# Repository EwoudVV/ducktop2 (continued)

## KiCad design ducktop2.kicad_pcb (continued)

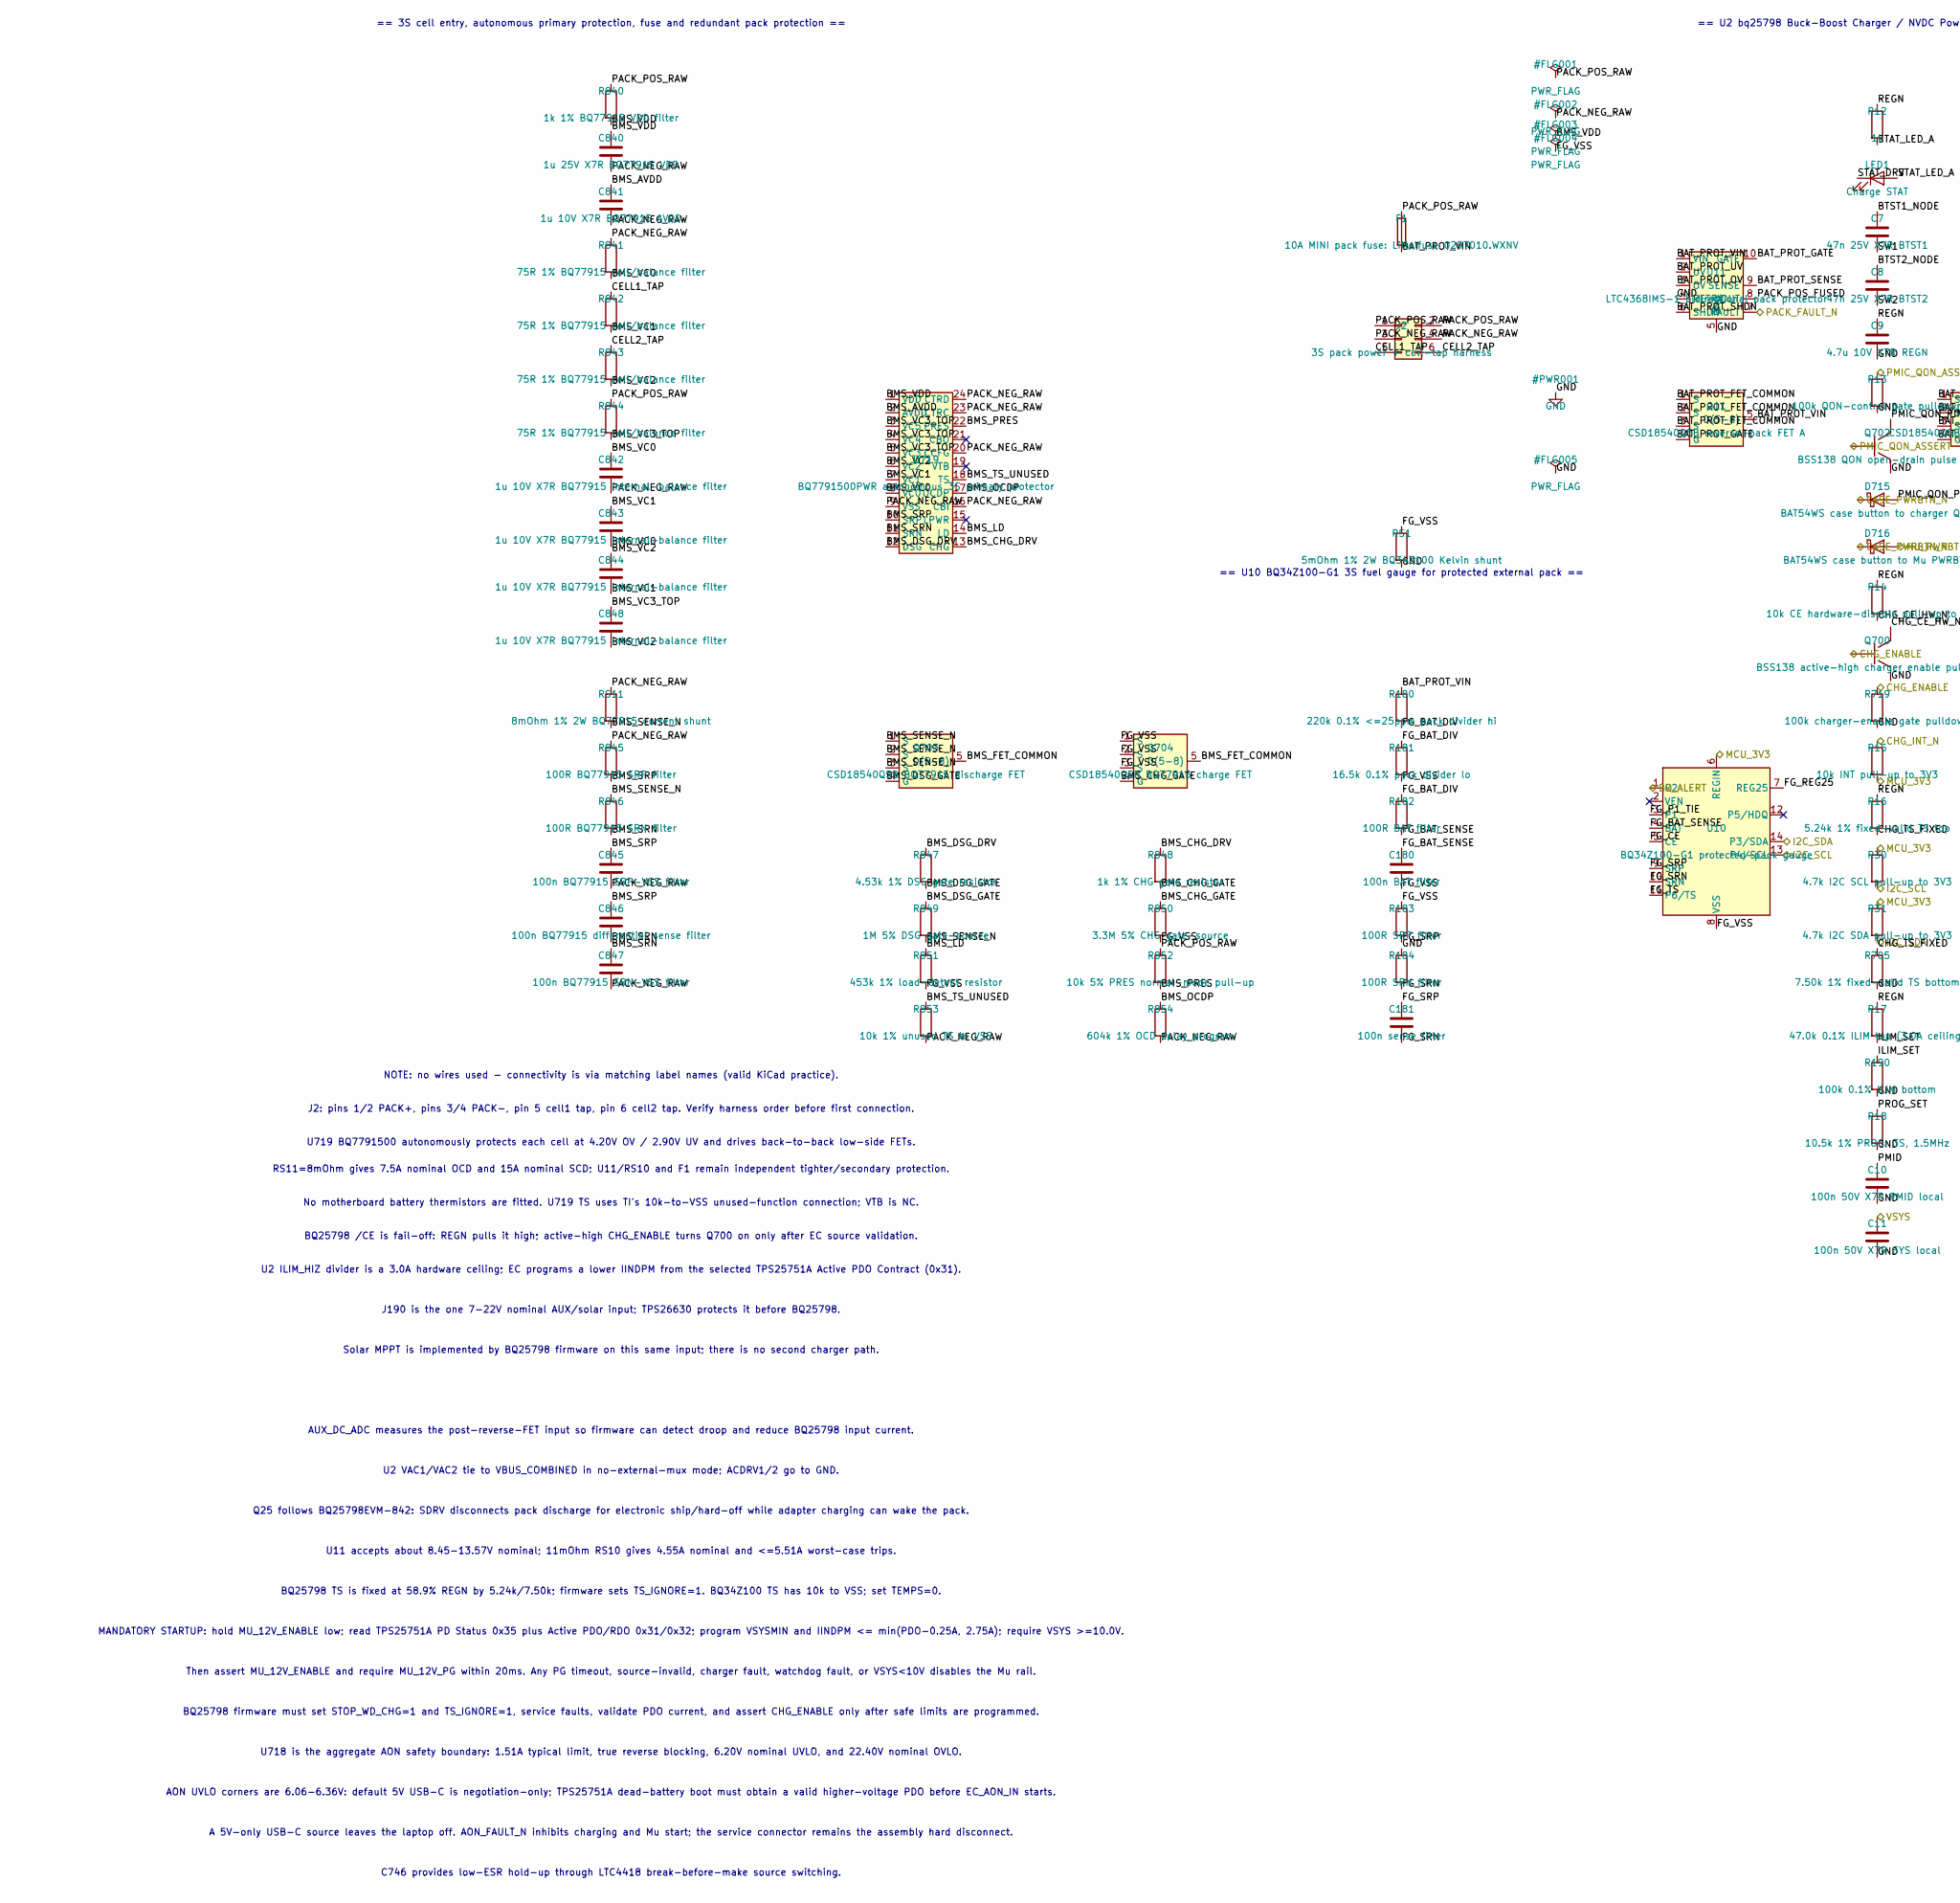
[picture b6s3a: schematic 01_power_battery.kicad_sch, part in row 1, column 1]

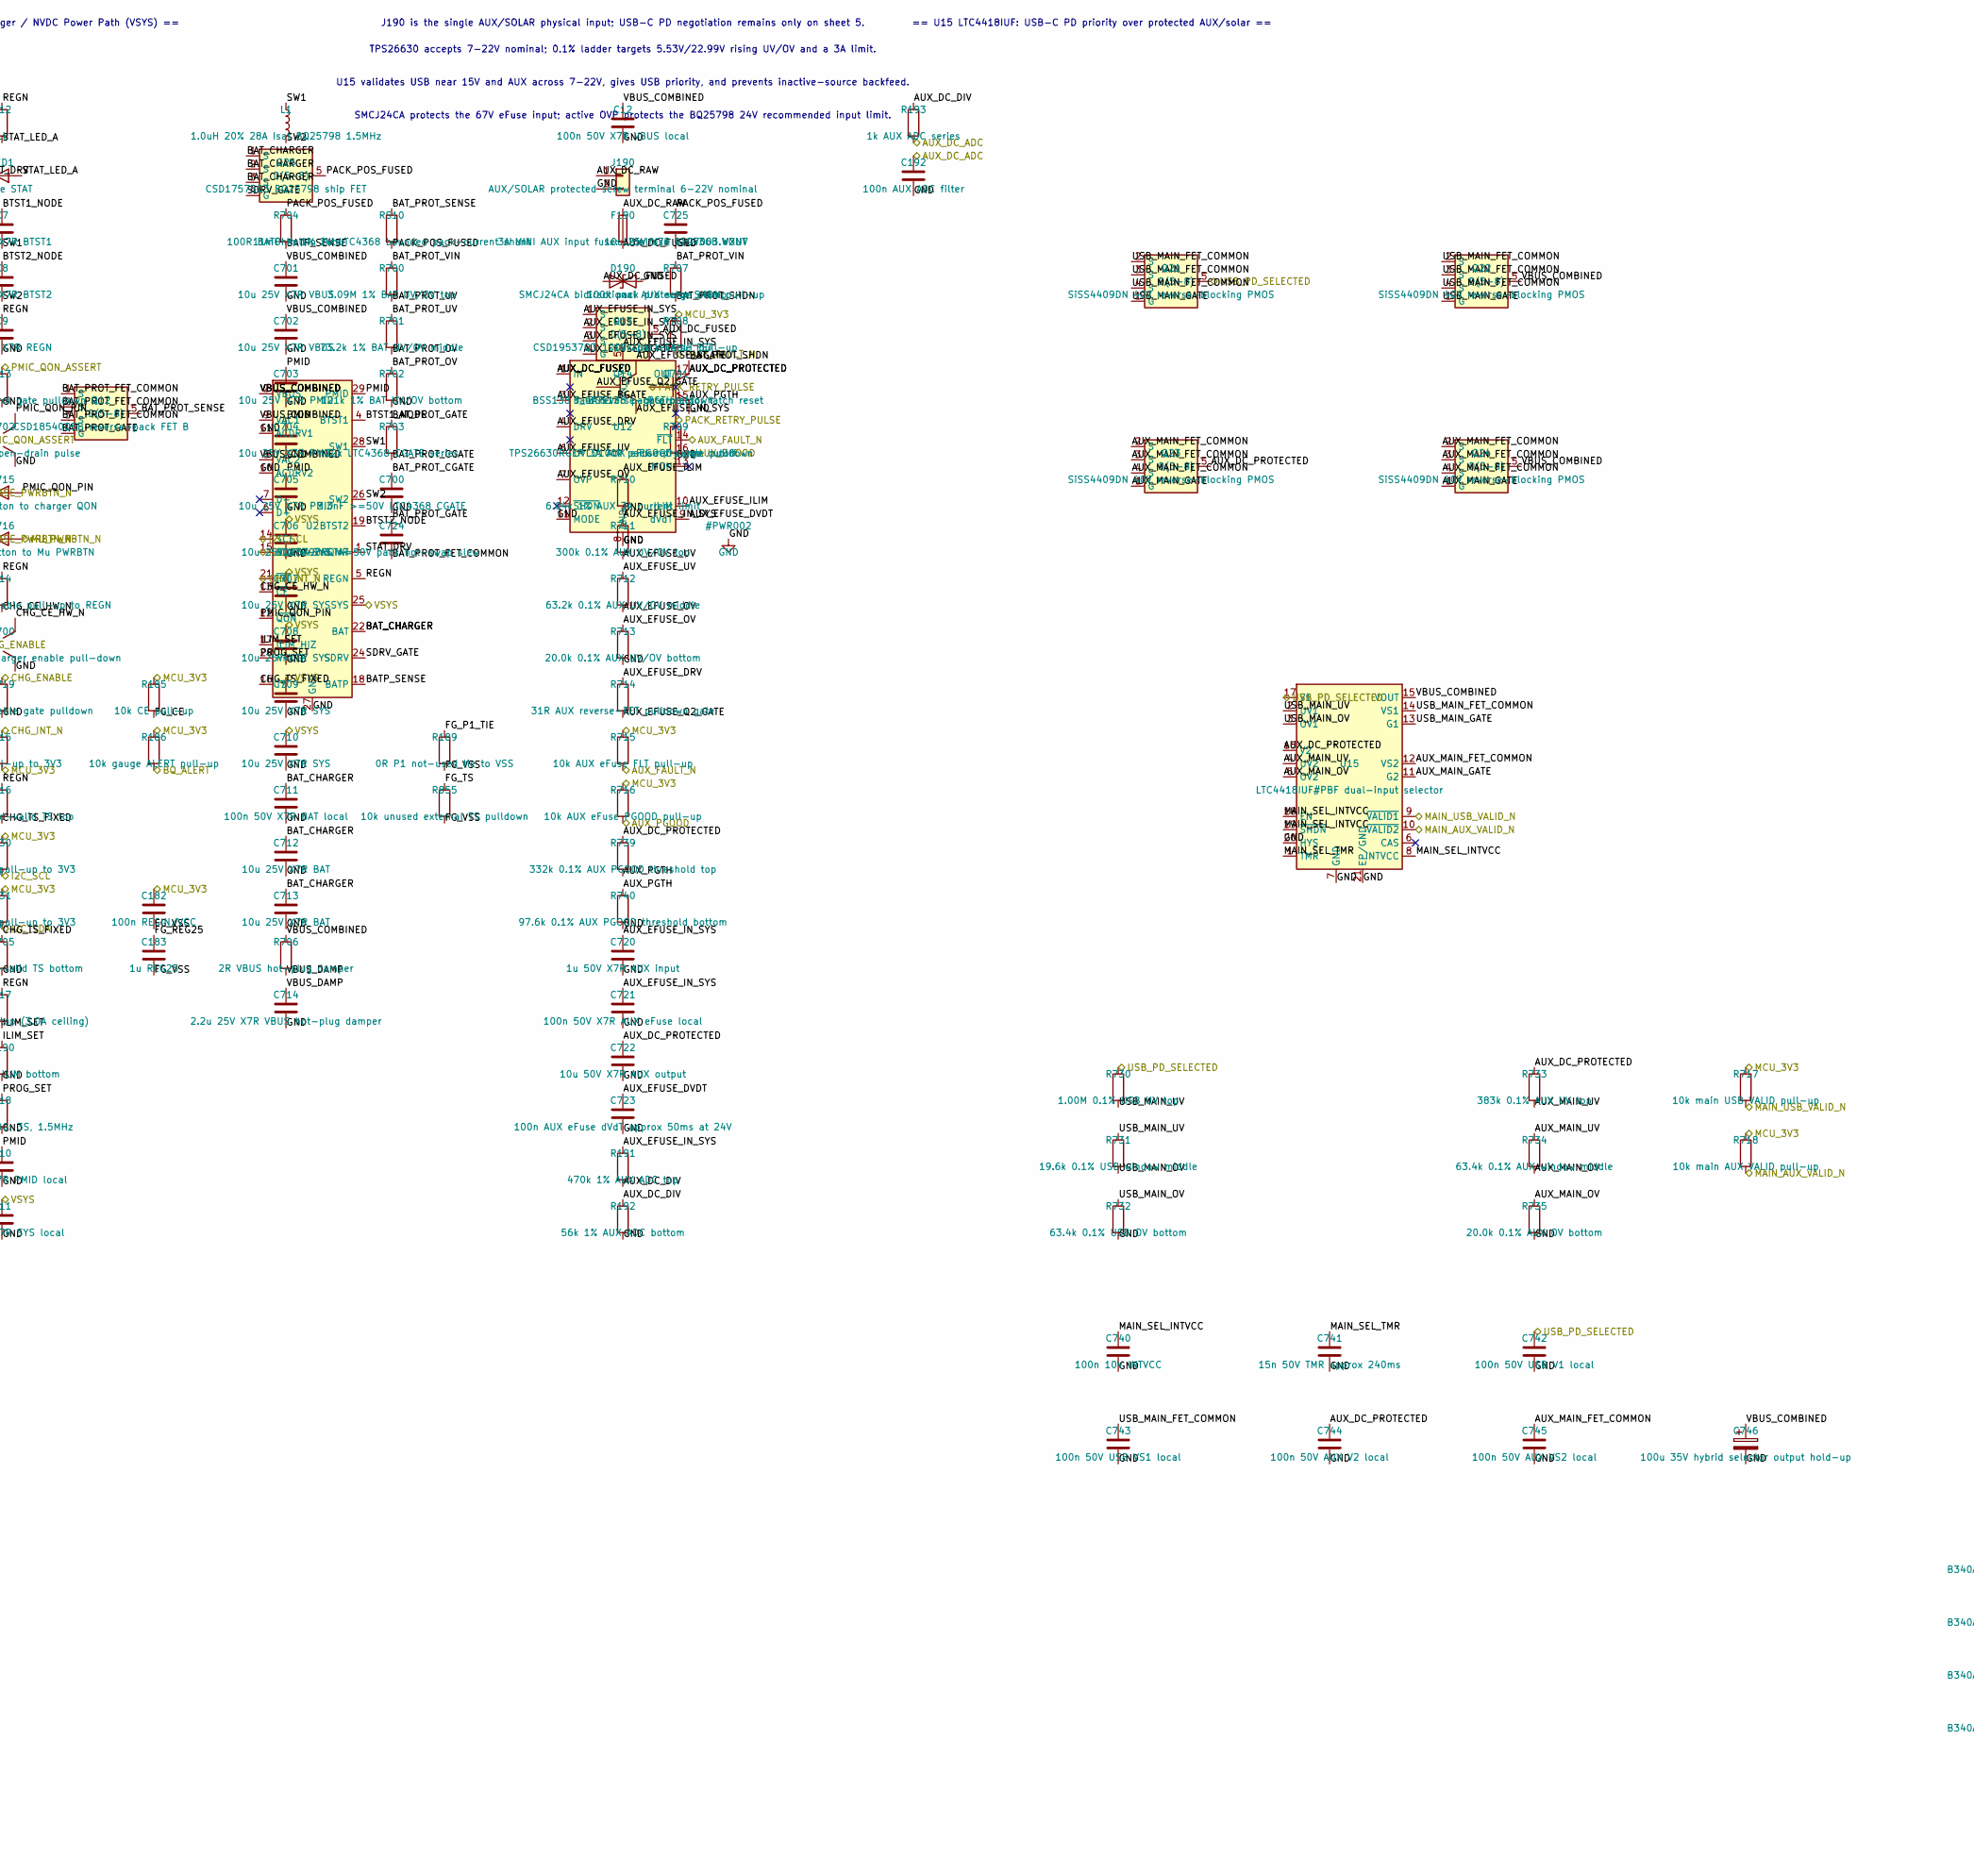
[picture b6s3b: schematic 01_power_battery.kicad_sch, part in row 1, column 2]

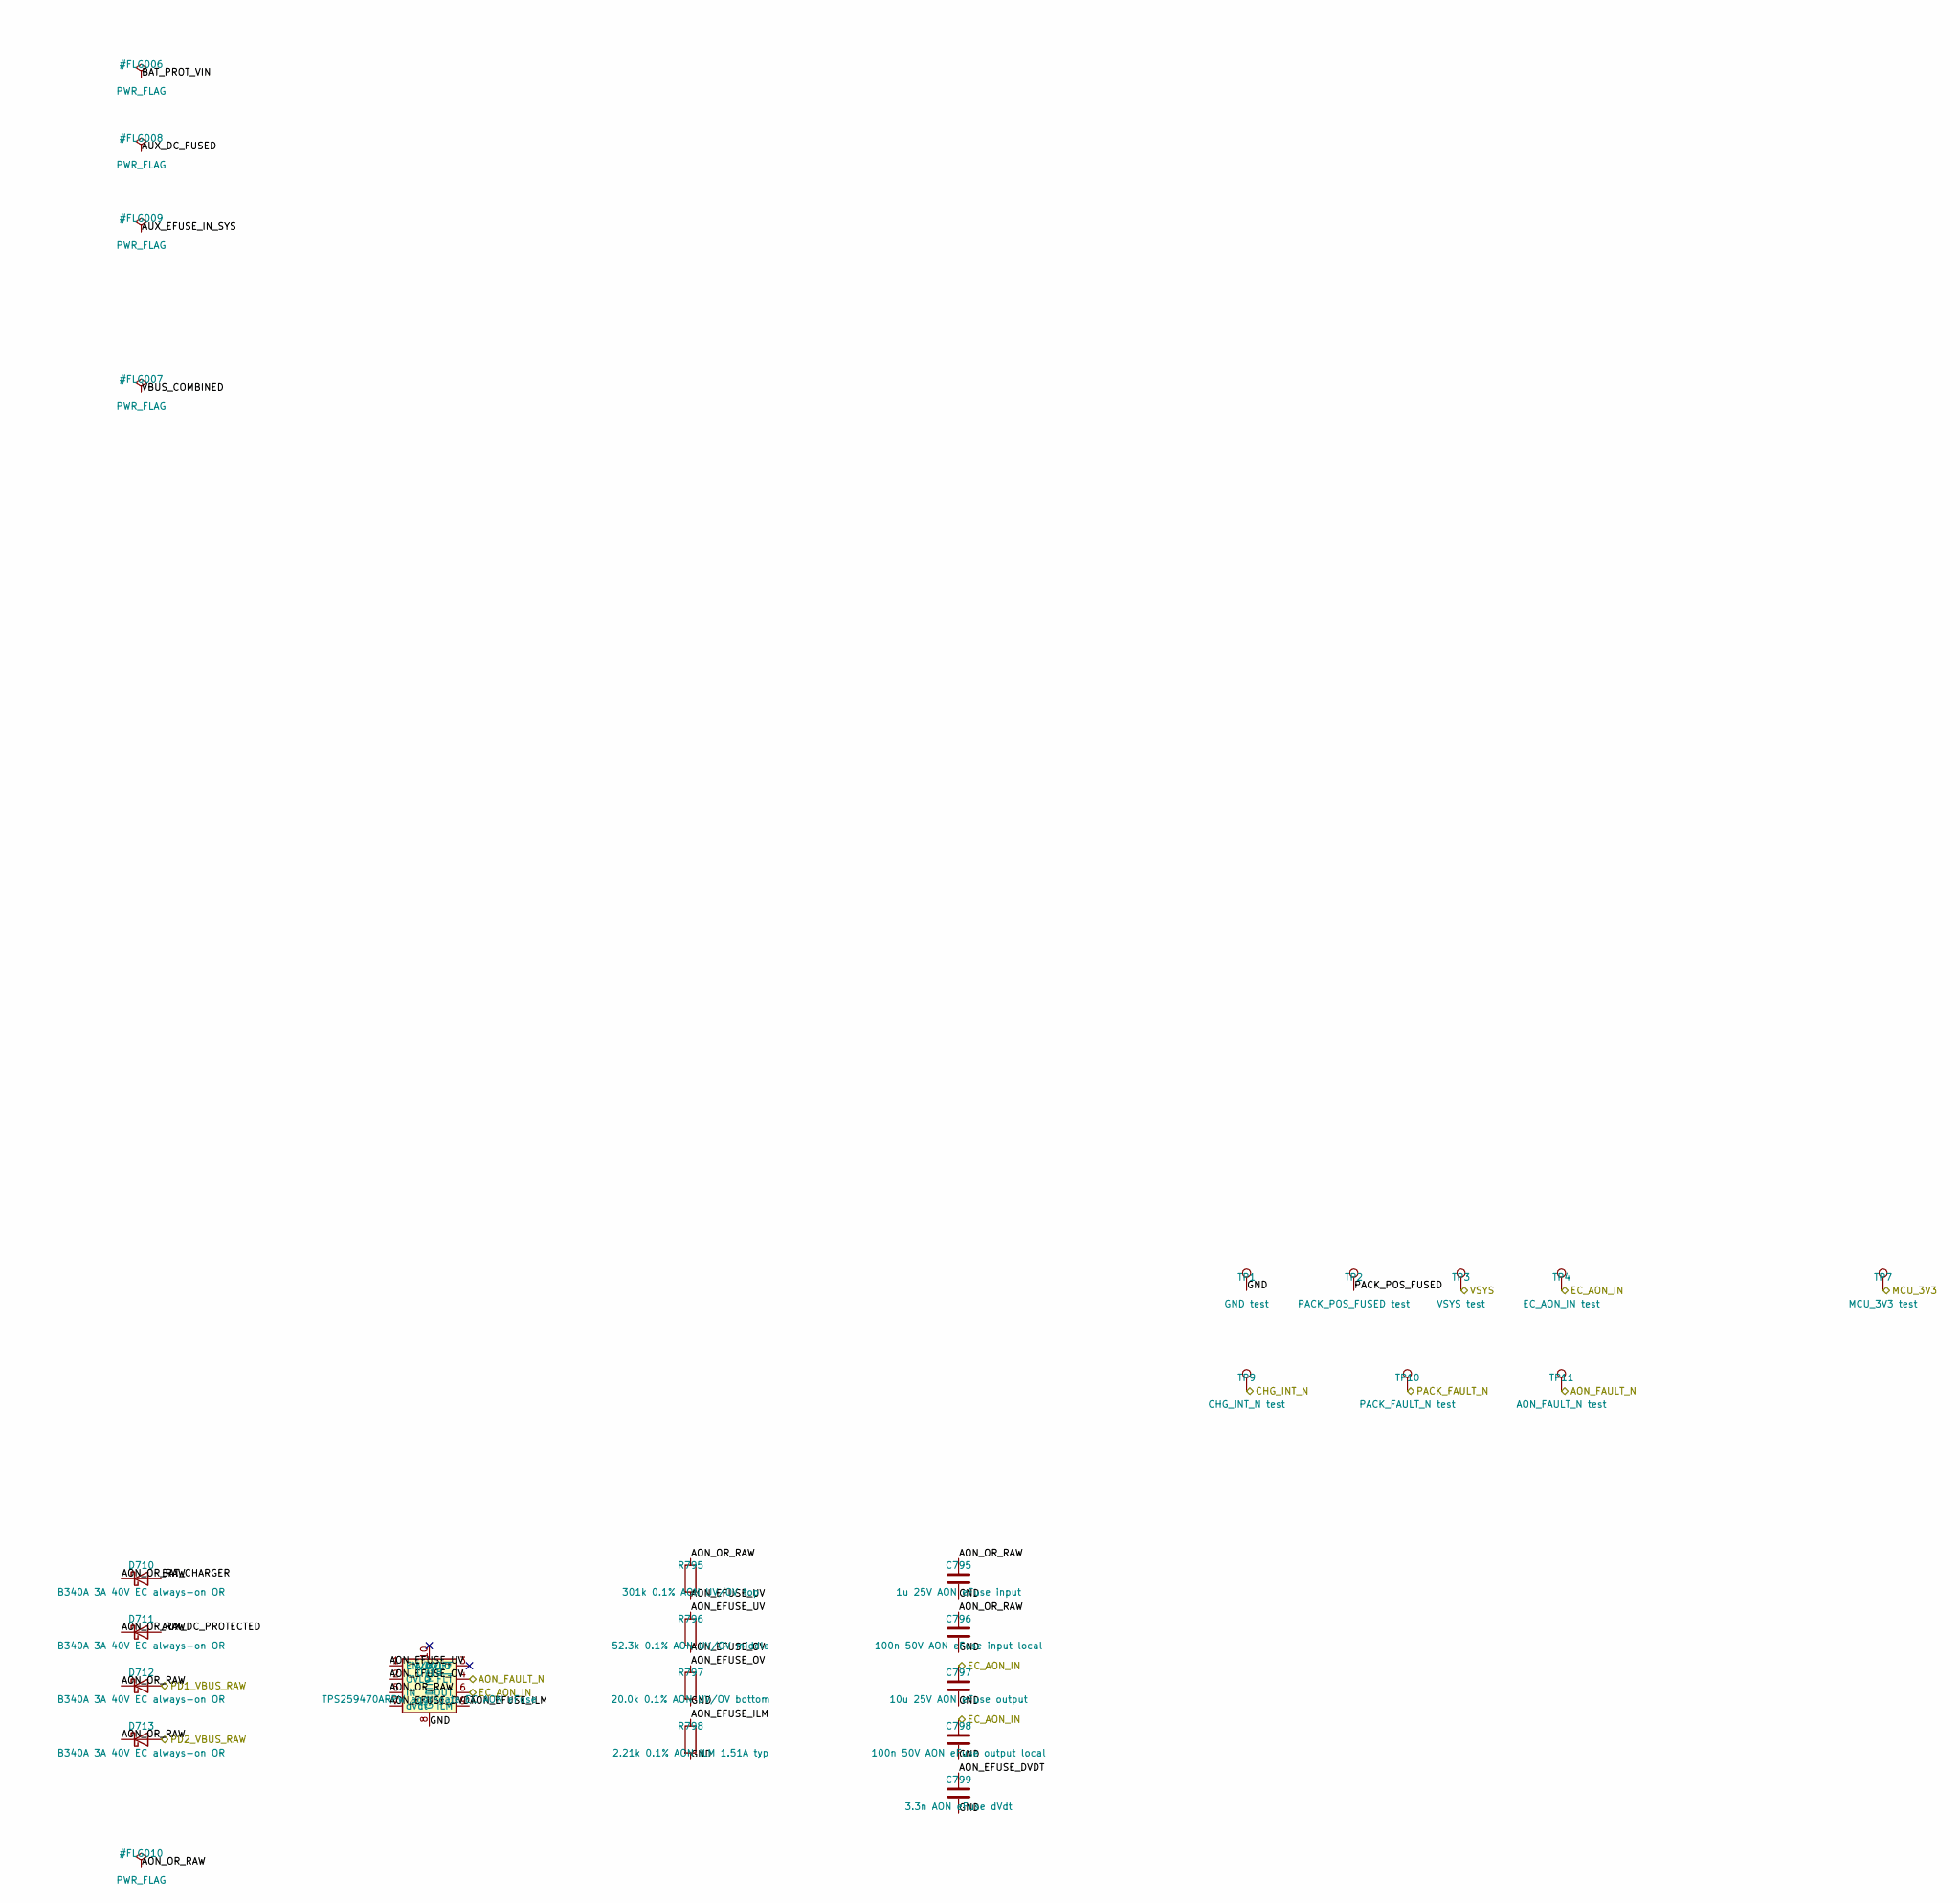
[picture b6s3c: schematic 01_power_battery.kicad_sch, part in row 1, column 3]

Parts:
C7: 47n 25V X7R BTST1; C_0402_1005Metric; MPN GRM155R71E473KA88D
C8: 47n 25V X7R BTST2; C_0402_1005Metric; MPN GRM155R71E473KA88D
C9: 4.7u 10V X7R REGN; C_0805_2012Metric; MPN GRM21BR71A475KA73L
C10: 100n 50V X7R PMID local; C_0603_1608Metric; MPN GRM188R71H104KA93D
C11: 100n 50V X7R SYS local; C_0603_1608Metric; MPN GRM188R71H104KA93D
C12: 100n 50V X7R VBUS local; C_0603_1608Metric; MPN GRM188R71H104KA93D
C180: 100n BAT filter; C_0603_1608Metric; MPN GRM188R71H104KA93D
C181: 100n sense filter; C_0603_1608Metric; MPN GRM188R71H104KA93D
C182: 100n REGIN/VCC; C_0603_1608Metric; MPN GRM188R71H104KA93D
C183: 1u REG25; C_0805_2012Metric; MPN GRM21BR71A105KA01L
C192: 100n AUX ADC filter; C_0603_1608Metric; MPN GRM188R71H104KA93D
C700: 3.3nF >=50V LTC4368 CGATE; C_0402_1005Metric; MPN GRM155R71H332KA01
C701, C702: 10u 25V X7R VBUS; C_1206_3216Metric; MPN GRM31CR71E106KA12L
C703, C704, C705: 10u 25V X7R PMID; C_1206_3216Metric; MPN GRM31CR71E106KA12L
C706, C707, C708, C709, C710: 10u 25V X7R SYS; C_1206_3216Metric; MPN GRM31CR71E106KA12L
C711: 100n 50V X7R BAT local; C_0603_1608Metric; MPN GRM188R71H104KA93D
C712, C713: 10u 25V X7R BAT; C_1206_3216Metric; MPN GRM31CR71E106KA12L
C714: 2.2u 25V X7R VBUS hot-plug damper; C_0805_2012Metric; MPN GRM21BR71E225KA73L
C720: 1u 50V X7R AUX input; C_0805_2012Metric; MPN GRM21BR71H105KA01
C721: 100n 50V X7R AUX eFuse local; C_0603_1608Metric; MPN GRM188R71H104KA93D
C722: 10u 50V X7R AUX output; C_1206_3216Metric; MPN CGA5L1X7R1H106K160AC
C723: 100n AUX eFuse dVdT approx 50ms at 24V; C_0603_1608Metric; MPN GRM188R71H104KA93D
C724: 4.7nF >=50V pack hot-swap slew; C_0402_1005Metric; MPN GRM155R71H472KA01
C725: 10u 25V X7R LTC4368 VOUT; C_0805_2012Metric; MPN GRM21BZ71E106KE15L
C740: 100n 10V INTVCC; C_0603_1608Metric; MPN GRM188R71A104KA61D
C741: 15n 50V TMR approx 240ms; C_0402_1005Metric; MPN GRM155R71H153KA12D
C742: 100n 50V USB V1 local; C_0603_1608Metric; MPN GRM188R71H104KA93D
C743: 100n 50V USB VS1 local; C_0603_1608Metric; MPN GRM188R71H104KA93D
C744: 100n 50V AUX V2 local; C_0603_1608Metric; MPN GRM188R71H104KA93D
C745: 100n 50V AUX VS2 local; C_0603_1608Metric; MPN GRM188R71H104KA93D
C746: 100u 35V hybrid selector output hold-up; CP_Elec_6.3x5.8; MPN EEHZK1V101XP
C795: 1u 25V AON eFuse input; C_0805_2012Metric; MPN GRM21BR71H105KA12L
C796: 100n 50V AON eFuse input local; C_0603_1608Metric; MPN GRM188R71H104KA93D
C797: 10u 25V AON eFuse output; C_1206_3216Metric; MPN GRM31CR71E106KA12L
C798: 100n 50V AON eFuse output local; C_0603_1608Metric; MPN GRM188R71H104KA93D
C799: 3.3n AON eFuse dVdt; C_0402_1005Metric; MPN GRM155R71H332KA01
C840: 1u 25V X7R BQ77915 VDD; C_0805_2012Metric; MPN GRM21BR71H105KA12L
C841: 1u 10V X7R BQ77915 AVDD; C_0805_2012Metric; MPN GRM21BR71A105KA01L
C842, C843, C844, C848: 1u 10V X7R BQ77915 internal-balance filter; C_0805_2012Metric; MPN GRM21BR71A105KA01L
C845: 100n BQ77915 SRP-VSS filter; C_0603_1608Metric; MPN GRM188R71H104KA93D
C846: 100n BQ77915 differential sense filter; C_0603_1608Metric; MPN GRM188R71H104KA93D
C847: 100n BQ77915 SRN-VSS filter; C_0603_1608Metric; MPN GRM188R71H104KA93D
D190: SMCJ24CA bidirectional AUX surge clamp; D_SMC; MPN SMCJ24CA-E3/57T
D710, D711, D712, D713: B340A 3A 40V EC always-on OR; D_SMA; MPN B340A-13-F
D715: BAT54WS case button to charger QON; D_SOD-323; MPN BAT54WS-7-F
D716: BAT54WS case button to Mu PWRBTN; D_SOD-323; MPN BAT54WS-7-F
F1: 10A MINI pack fuse: Littelfuse 0297010.WXNV; Fuseholder_Blade_Mini_Keystone_3568; MPN 0297010.WXNV + 3568
F190: 3A MINI AUX input fuse: Littelfuse 0297003.WXNV; Fuseholder_Blade_Mini_Keystone_3568; MPN 0297003.WXNV + 3568
J2: 3S pack power + cell-tap harness; Molex_Mega-Fit_76829-0006_2x03_P5.70mm_Vertical; MPN 76829-0006
J190: AUX/SOLAR protected screw terminal 6-22V nominal; TerminalBlock_Phoenix_MKDS-1,5-2-5.08_1x02_P5.08mm_Horizont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; MPN 1715022
L1: 1.0uH 20% 28A Isat BQ25798 1.5MHz; L_Coilcraft_XAL7030-102; MPN XAL7030-102MEC
LED1: Charge STAT; LED_0603_1608Metric; MPN APT1608SGC
Q11: CSD18540Q5B reverse-pack FET A; CSD18540Q5B_DNK; MPN CSD18540Q5B
Q12: CSD18540Q5B reverse-pack FET B; CSD18540Q5B_DNK; MPN CSD18540Q5B
Q13: CSD19537Q3 100V AUX reverse FET; CSD19537Q3_DQG; MPN CSD19537Q3
Q14: BSS138 fast reverse-gate pulldown; SOT-23; MPN BSS138LT1G
Q21, Q22, Q23, Q24: SiSS4409DN 40V reverse-blocking PMOS; Vishay_PowerPAK_1212-8_Single; MPN SiSS4409DN-T1-GE3
Q25: CSD17575Q3 BQ25798 ship FET; CSD19537Q3_DQG; MPN CSD17575Q3
Q700: BSS138 active-high charger enable pull-down; SOT-23; MPN BSS138LT1G
Q701: BSS138 pack protector latch reset; SOT-23; MPN BSS138LT1G
Q702: BSS138 QON open-drain pulse; SOT-23; MPN BSS138LT1G
Q703: CSD18540Q5B BQ77915 discharge FET; CSD18540Q5B_DNK; MPN CSD18540Q5B
Q704: CSD18540Q5B BQ77915 charge FET; CSD18540Q5B_DNK; MPN CSD18540Q5B
R12: 1k; R_0603_1608Metric; MPN RC0603FR-071KL
R13: 100k QON-control gate pulldown; R_0603_1608Metric; MPN RC0603FR-07100KL
R14: 10k CE hardware-disable pull-up to REGN; R_0603_1608Metric; MPN RC0603FR-0710KL
R15: 10k INT pull-up to 3V3; R_0603_1608Metric; MPN RC0603FR-0710KL
R16: 5.24k 1% fixed-valid TS top; R_0603_1608Metric; MPN RC0603FR-075K24L
R17: 47.0k 0.1% ILIM top (3.0A ceiling); R_0603_1608Metric; MPN RT0603BRD0747KL
R18: 10.5k 1% PROG: 3S, 1.5MHz; R_0603_1608Metric; MPN RC0603FR-0710K5L
R30: 4.7k I2C SCL pull-up to 3V3; R_0603_1608Metric; MPN RC0603FR-074K7L
R31: 4.7k I2C SDA pull-up to 3V3; R_0603_1608Metric; MPN RC0603FR-074K7L
R180: 220k 0.1% <=25ppm pack divider hi; R_0603_1608Metric; MPN RT0603BRD07220KL
R181: 16.5k 0.1% pack divider lo; R_0603_1608Metric; MPN RT0603BRD0716K5L
R182: 100R BAT filter; R_0603_1608Metric; MPN RC0603FR-07100RL
R183: 100R SRP filter; R_0603_1608Metric; MPN RC0603FR-07100RL
R184: 100R SRN filter; R_0603_1608Metric; MPN RC0603FR-07100RL
R185: 10k CE pull-up; R_0603_1608Metric; MPN RC0603FR-0710KL
R186: 10k gauge ALERT pull-up; R_0603_1608Metric; MPN RC0603FR-0710KL
R189: 0R P1 not-used tie to VSS; R_0603_1608Metric; MPN RC0603FR-070RL
R190: 100k 0.1% ILIM bottom; R_0603_1608Metric; MPN RT0603BRD07100KL
R191: 470k 1% AUX ADC top; R_0603_1608Metric; MPN RC0603FR-07470KL
R192: 56k 1% AUX ADC bottom; R_0603_1608Metric; MPN RC0603FR-0756KL
R193: 1k AUX ADC series; R_0603_1608Metric; MPN RC0603FR-071KL
R700: 3.09M 1% BAT UV/OV top; R_0603_1608Metric; MPN RC0603FR-073M09L
R701: 73.2k 1% BAT UV/OV middle; R_0603_1608Metric; MPN RC0603FR-0773K2L
R702: 121k 1% BAT UV/OV bottom; R_0603_1608Metric; MPN RC0603FR-07121KL
R703: 22k LTC4368 CGATE series; R_0603_1608Metric; MPN RC0603FR-0722KL
R704: 100R BATP Kelvin filter; R_0603_1608Metric; MPN RC0603FR-07100RL
R705: 7.50k 1% fixed-valid TS bottom; R_0603_1608Metric; MPN RC0603FR-077K50L
R706: 2R VBUS hot-plug damper; R_0603_1608Metric; MPN RC0603FR-072RL
R707: 100k pack protector SHDN pull-up; R_0603_1608Metric; MPN RC0603FR-07100KL
R708: 10k pack FAULT pull-up; R_0603_1608Metric; MPN RC0603FR-0710KL
R709: 100k pack retry gate pulldown; R_0603_1608Metric; MPN RC0603FR-07100KL
R710: 6.04k 1% AUX 3A current limit; R_0603_1608Metric; MPN RC0603FR-076K04L
R711: 300k 0.1% AUX UV/OV top; R_0603_1608Metric; MPN RT0603BRD07300KL
R712: 63.2k 0.1% AUX UV/OV middle; R_0603_1608Metric; MPN RT0603BRD0763K2L
R713: 20.0k 0.1% AUX UV/OV bottom; R_0603_1608Metric; MPN RT0603BRD0720K0L
R714: 31R AUX reverse-FET pulldown gate; R_0603_1608Metric; MPN RC0603FR-0731RL
R715: 10k AUX eFuse FLT pull-up; R_0603_1608Metric; MPN RC0603FR-0710KL
R716: 10k AUX eFuse PGOOD pull-up; R_0603_1608Metric; MPN RC0603FR-0710KL
R717: 10k main USB VALID pull-up; R_0603_1608Metric; MPN RC0603FR-0710KL
R718: 10k main AUX VALID pull-up; R_0603_1608Metric; MPN RC0603FR-0710KL
R719: 100k charger-enable gate pulldown; R_0603_1608Metric; MPN RC0603FR-07100KL
R730: 1.00M 0.1% USB UV top; R_0603_1608Metric; MPN RT0603BRD071ML
R731: 19.6k 0.1% USB window middle; R_0603_1608Metric; MPN RT0603BRD0719K6L
R732: 63.4k 0.1% USB OV bottom; R_0603_1608Metric; MPN RT0603BRD0763K4L
R733: 383k 0.1% AUX UV top; R_0603_1608Metric; MPN RT0603BRD07383KL
R734: 63.4k 0.1% AUX window middle; R_0603_1608Metric; MPN RT0603BRD0763K4L
R735: 20.0k 0.1% AUX OV bottom; R_0603_1608Metric; MPN RT0603BRD0720KL
R739: 332k 0.1% AUX PGOOD threshold top; R_0603_1608Metric; MPN RT0603BRD07332KL
R740: 97.6k 0.1% AUX PGOOD threshold bottom; R_0603_1608Metric; MPN RT0603BRD0797K6L
R795: 301k 0.1% AON UV/OV top; R_0603_1608Metric; MPN RT0603BRD07301KL
R796: 52.3k 0.1% AON UV/OV middle; R_0603_1608Metric; MPN RT0603BRD0752K3L
R797: 20.0k 0.1% AON UV/OV bottom; R_0603_1608Metric; MPN RT0603BRD0720KL
R798: 2.21k 0.1% AON ILM 1.51A typ; R_0603_1608Metric; MPN RT0603BRD072K21L
R840: 1k 1% BQ77915 VDD filter; R_0603_1608Metric; MPN RC0603FR-071KL
R841, R842, R843, R844: 75R 1% BQ77915 cell/balance filter; R_0603_1608Metric; MPN RC0603FR-0775RL
R845: 100R BQ77915 SRP filter; R_0603_1608Metric; MPN RC0603FR-07100RL
R846: 100R BQ77915 SRN filter; R_0603_1608Metric; MPN RC0603FR-07100RL
R847: 4.53k 1% DSG gate resistor; R_0603_1608Metric; MPN RC0603FR-074K53L
R848: 1k 1% CHG gate resistor; R_0603_1608Metric; MPN RC0603FR-071KL
R849: 1M 5% DSG gate-source; R_0603_1608Metric; MPN RC0603FR-071ML
R850: 3.3M 5% CHG gate-source; R_0603_1608Metric; MPN RC0603FR-073M3L
R851: 453k 1% load-detect resistor; R_0603_1608Metric; MPN RC0603FR-07453KL
R852: 10k 5% PRES normal-mode pull-up; R_0603_1608Metric; MPN RC0603FR-0710KL
R853: 10k 1% unused TS to VSS; R_0603_1608Metric; MPN RC0603FR-0710KL
R854: 604k 1% OCD delay program; R_0603_1608Metric; MPN RC0603FR-07604KL
R855: 10k unused external TS pulldown; R_0603_1608Metric; MPN RC0603FR-0710KL
RS1: 5mOhm 1% 2W BQ34Z100 Kelvin shunt; R_2512_6332Metric; MPN WSLP2512R0050FEA
RS10: 11mOhm 1% 2W LTC4368 bounded pack-current shunt; R_2512_6332Metric; MPN WSLP2512R0110FEA
RS11: 8mOhm 1% 2W BQ77915 current shunt; R_2512_6332Metric; MPN WSLP25128L000FEA
TP1: GND test; TestPoint_Pad_D1.0mm
TP2: PACK_POS_FUSED test; TestPoint_Pad_D1.0mm
TP3: VSYS test; TestPoint_Pad_D1.0mm
TP4: EC_AON_IN test; TestPoint_Pad_D1.0mm
TP7: MCU_3V3 test; TestPoint_Pad_D1.0mm
TP9: CHG_INT_N test; TestPoint_Pad_D1.0mm
TP10: PACK_FAULT_N test; TestPoint_Pad_D1.0mm
TP11: AON_FAULT_N test; TestPoint_Pad_D1.0mm
U2: BQ25798RQMR; Texas_RQM0029A_VQFN-29_4x4mm_P0.4mm; MPN BQ25798RQMR
U10: BQ34Z100-G1 protected-pack gauge; TSSOP-14_4.4x5mm_P0.65mm; MPN BQ34Z100PWR-G1
U11: LTC4368IMS-1 bidirectional pack protector; MSOP-10_3x3mm_P0.5mm; MPN LTC4368IMS-1#PBF
U12: TPS26630RGER 3A AUX eFuse / surge cutoff; Texas_RGE0024H_VQFN-24-1EP_4x4mm_P0.5mm_EP2.7x2.7mm_Thermal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; MPN TPS26630RGER
U15: LTC4418IUF#PBF dual-input selector; ADI_UF20_QFN20_4x4_P0.5_EP2.45; MPN LTC4418IUF#PBF
U718: TPS259470ARPW aggregate EC AON eFuse; Texas_RPW0010A_VQFN-HR-10_2x2mm; MPN TPS259470ARPW
U719: BQ7791500PWR autonomous 3S primary protector; TSSOP-24_4.4x7.8mm_P0.65mm; MPN BQ7791500PWR

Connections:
/AON_FAULT_N: TP11.1 (1_1), U718.4 (~FLT); also elsewhere on the board
/AUX_DC_ADC: C192.1, R193.2; also elsewhere on the board
/AUX_FAULT_N: R715.2, U12.14 (~FLT); also elsewhere on the board
/AUX_PGOOD: R716.2, U12.16 (PGOOD); also elsewhere on the board
/BQ_ALERT: R186.2, U10.1 (P2); also elsewhere on the board
/CASE_PWRBTN_N: D715.1 (K), D716.1 (K); also elsewhere on the board
/CHG_ENABLE: Q700.1 (G), R719.1; also elsewhere on the board
/CHG_INT_N: R15.1, TP9.1 (1_1), U2.21 (~INT); also elsewhere on the board
/EC_AON_IN: C797.1, C798.1, TP4.1 (1_1), U718.6 (OUT); also elsewhere on the board
/I2C_SCL: R30.2, U2.14 (SCL), U10.13 (P4/SCL); also elsewhere on the board
/I2C_SDA: R31.2, U2.15 (SDA), U10.14 (P3/SDA); also elsewhere on the board
/MAIN_AUX_VALID_N: R718.2, U15.10 (~VALID2); also elsewhere on the board
/MAIN_USB_VALID_N: R717.2, U15.9 (~VALID1); also elsewhere on the board
/MCU_3V3: C182.1, R15.2, R30.1, R31.1, R185.1, R186.1, R708.1, R715.1, R716.1, R717.1, R718.1, TP7.1 (1_1), U10.6 (REGIN); also elsewhere on the board
/MU_PWRBTN_N: D716.2 (A); also elsewhere on the board
/PACK_FAULT_N: R708.2, TP10.1 (1_1), U11.7 (FAULT); also elsewhere on the board
/PACK_RETRY_PULSE: Q701.1 (G), R709.1; also elsewhere on the board
/PD1_VBUS_RAW: D712.2 (A); also elsewhere on the board
/PD2_VBUS_RAW: D713.2 (A); also elsewhere on the board
/PMIC_QON_ASSERT: Q702.1 (G), R13.1; also elsewhere on the board
/Power & Battery/AON_EFUSE_DVDT: C799.1, U718.7 (dVdt)
/Power & Battery/AON_EFUSE_ILM: R798.1, U718.9 (ILM)
/Power & Battery/AON_EFUSE_OV: R796.2, R797.1, U718.2 (OVLO)
/Power & Battery/AON_EFUSE_UV: R795.2, R796.1, U718.1 (EN/UVLO)
/Power & Battery/AON_OR_RAW: C795.1, C796.1, D710.1 (K), D711.1 (K), D712.1 (K), D713.1 (K), R795.1, U718.5 (IN)
/Power & Battery/AUX_DC_DIV: R191.2, R192.1, R193.1
/Power & Battery/AUX_DC_FUSED: D190.1 (A1), F190.2, Q13.5 (D(5-8)), U12.1 (IN), U12.2 (IN)
/Power & Battery/AUX_DC_PROTECTED: C722.1, C744.1, D711.2 (A), Q23.5 (D(5-8)), R733.1, R739.1, U12.17 (OUT), U12.18 (OUT), U15.16 (V2)
/Power & Battery/AUX_DC_RAW: F190.1, J190.1
/Power & Battery/AUX_EFUSE_BGATE: Q13.4 (G), Q14.3 (D), U12.3 (B_GATE)
/Power & Battery/AUX_EFUSE_DRV: R714.1, U12.4 (DRV)
/Power & Battery/AUX_EFUSE_DVDT: C723.1, U12.9 (dVdT)
/Power & Battery/AUX_EFUSE_ILIM: R710.1, U12.10 (ILIM)
/Power & Battery/AUX_EFUSE_IN_SYS: C720.1, C721.1, Q13.1 (S), Q13.2 (S), Q13.3 (S), Q14.2 (S), R191.1, R711.1, U12.5 (IN_SYS)
/Power & Battery/AUX_EFUSE_OV: R712.2, R713.1, U12.7 (OVP)
/Power & Battery/AUX_EFUSE_Q2_GATE: Q14.1 (G), R714.2
/Power & Battery/AUX_EFUSE_UV: R711.2, R712.1, U12.6 (UVLO)
/Power & Battery/AUX_MAIN_FET_COMMON: C745.1, Q23.2 (S), Q23.3 (S), Q23.4 (S), Q24.2 (S), Q24.3 (S), Q24.4 (S), U15.12 (VS2)
/Power & Battery/AUX_MAIN_GATE: Q23.1 (G), Q24.1 (G), U15.11 (G2)
/Power & Battery/AUX_MAIN_OV: R734.2, R735.1, U15.5 (OV2)
/Power & Battery/AUX_MAIN_UV: R733.2, R734.1, U15.4 (UV2)
/Power & Battery/AUX_PGTH: R739.2, R740.1, U12.15 (PGTH)
/Power & Battery/BATP_SENSE: R704.2, U2.18 (BATP)
/Power & Battery/BAT_CHARGER: C711.1, C712.1, C713.1, D710.2 (A), Q25.1 (S), Q25.2 (S), Q25.3 (S), U2.22 (BAT), U2.23 (BAT)
/Power & Battery/BAT_PROT_CGATE: C700.1, R703.2
/Power & Battery/BAT_PROT_FET_COMMON: C724.2, Q11.1 (S), Q11.2 (S), Q11.3 (S), Q12.1 (S), Q12.2 (S), Q12.3 (S)
/Power & Battery/BAT_PROT_GATE: C724.1, Q11.4 (G), Q12.4 (G), R703.1, U11.10 (GATE)
/Power & Battery/BAT_PROT_OV: R701.2, R702.1, U11.3 (OV)
/Power & Battery/BAT_PROT_SENSE: Q12.5 (D(5-8)), RS10.1, U11.9 (SENSE)
/Power & Battery/BAT_PROT_SHDN: Q701.3 (D), R707.2, U11.6 (SHDN)
/Power & Battery/BAT_PROT_UV: R700.2, R701.1, U11.2 (UV)
/Power & Battery/BAT_PROT_VIN: F1.2, Q11.5 (D(5-8)), R180.1, R700.1, R707.1, U11.1 (VIN)
/Power & Battery/BMS_AVDD: C841.1, U719.2 (AVDD)
/Power & Battery/BMS_CHG_DRV: R848.1, U719.13 (CHG)
/Power & Battery/BMS_CHG_GATE: Q704.4 (G), R848.2, R850.1
/Power & Battery/BMS_DSG_DRV: R847.1, U719.12 (DSG)
/Power & Battery/BMS_DSG_GATE: Q703.4 (G), R847.2, R849.1
/Power & Battery/BMS_FET_COMMON: Q703.5 (D(5-8)), Q704.5 (D(5-8))
/Power & Battery/BMS_LD: R851.1, U719.14 (LD)
/Power & Battery/BMS_OCDP: R854.1, U719.17 (OCDP)
/Power & Battery/BMS_PRES: R852.2, U719.22 (PRES)
/Power & Battery/BMS_SENSE_N: Q703.1 (S), Q703.2 (S), Q703.3 (S), R846.1, R849.2, RS11.2
/Power & Battery/BMS_SRN: C846.2, C847.1, R846.2, U719.11 (SRN)
/Power & Battery/BMS_SRP: C845.1, C846.1, R845.2, U719.10 (SRP)
/Power & Battery/BMS_TS_UNUSED: R853.1, U719.18 (TS)
/Power & Battery/BMS_VC0: C842.1, C843.2, R841.2, U719.8 (VC0)
/Power & Battery/BMS_VC1: C843.1, C844.2, R842.2, U719.7 (VC1)
/Power & Battery/BMS_VC2: C844.1, C848.2, R843.2, U719.6 (VC2)
/Power & Battery/BMS_VC3_TOP: C848.1, R844.2, U719.3 (VC5), U719.4 (VC4), U719.5 (VC3)
/Power & Battery/BMS_VDD: C840.1, R840.2, U719.1 (VDD)
/Power & Battery/BTST1_NODE: C7.1, U2.4 (BTST1)
/Power & Battery/BTST2_NODE: C8.1, U2.19 (BTST2)
/Power & Battery/CELL1_TAP: J2.5, R842.1
/Power & Battery/CELL2_TAP: J2.6, R843.1
/Power & Battery/CHG_CE_HW_N: Q700.3 (D), R14.2, U2.13 (~CE)
/Power & Battery/CHG_TS_FIXED: R16.2, R705.1, U2.16 (TS)
/Power & Battery/FG_BAT_DIV: R180.2, R181.1, R182.1
/Power & Battery/FG_BAT_SENSE: C180.1, R182.2, U10.4 (BAT)
/Power & Battery/FG_CE: R185.2, U10.5 (CE)
/Power & Battery/FG_P1_TIE: R189.1, U10.3 (P1)
/Power & Battery/FG_REG25: C183.1, U10.7 (REG25)
/Power & Battery/FG_SRN: C181.2, R184.2, U10.10 (SRN)
/Power & Battery/FG_SRP: C181.1, R183.2, U10.9 (SRP)
/Power & Battery/FG_TS: R855.1, U10.11 (P6/TS)
/Power & Battery/FG_VSS: C180.2, C182.2, C183.2, Q704.1 (S), Q704.2 (S), Q704.3 (S), R181.2, R183.1, R189.2, R850.2, R851.2, R855.2, RS1.1, U10.8 (VSS)
/Power & Battery/ILIM_SET: R17.2, R190.1, U2.17 (ILIM_HIZ)
/Power & Battery/MAIN_SEL_INTVCC: C740.1, U15.8 (INTVCC), U15.18 (EN), U15.19 (~SHDN)
/Power & Battery/MAIN_SEL_TMR: C741.1, U15.1 (TMR)
/Power & Battery/PACK_NEG_RAW: C840.2, C841.2, C842.2, C845.2, C847.2, J2.3, J2.4, R841.1, R845.1, R853.2, R854.2, RS11.1, U719.9 (VSS), U719.16 (CBI), U719.20 (CCFG), U719.23 (CTRC), U719.24 (CTRD)
/Power & Battery/PACK_POS_FUSED: C725.1, Q25.5 (D(5-8)), R704.1, RS10.2, TP2.1 (1_1), U11.8 (VOUT)
/Power & Battery/PACK_POS_RAW: F1.1, J2.1, J2.2, R840.1, R844.1, R852.1
/Power & Battery/PMIC_QON_PIN: D715.2 (A), Q702.3 (D), U2.12 (~QON)
/Power & Battery/PMID: C10.1, C703.1, C704.1, C705.1, U2.29 (PMID)
/Power & Battery/PROG_SET: R18.1, U2.20 (PROG)
/Power & Battery/REGN: C9.1, R12.1, R14.1, R16.1, R17.1, U2.5 (REGN)
/Power & Battery/SDRV_GATE: Q25.4 (G), U2.24 (SDRV)
/Power & Battery/STAT_DRV: LED1.1 (K), U2.1 (STAT)
/Power & Battery/STAT_LED_A: LED1.2 (A), R12.2
/Power & Battery/SW1: C7.2, L1.1, U2.28 (SW1)
/Power & Battery/SW2: C8.2, L1.2, U2.26 (SW2)
/Power & Battery/USB_MAIN_FET_COMMON: C743.1, Q21.2 (S), Q21.3 (S), Q21.4 (S), Q22.2 (S), Q22.3 (S), Q22.4 (S), U15.14 (VS1)
/Power & Battery/USB_MAIN_GATE: Q21.1 (G), Q22.1 (G), U15.13 (G1)
/Power & Battery/USB_MAIN_OV: R731.2, R732.1, U15.3 (OV1)
/Power & Battery/USB_MAIN_UV: R730.2, R731.1, U15.2 (UV1)
/Power & Battery/VBUS_COMBINED: C12.1, C701.1, C702.1, C746.1, Q22.5 (D(5-8)), Q24.5 (D(5-8)), R706.1, U2.2 (VBUS), U2.3 (VBUS), U2.8 (VAC2), U2.9 (VAC1), U15.15 (VOUT)
/Power & Battery/VBUS_DAMP: C714.1, R706.2
/USB_PD_SELECTED: C742.1, Q21.5 (D(5-8)), R730.1, U15.17 (V1); also elsewhere on the board
/VSYS: C11.1, C706.1, C707.1, C708.1, C709.1, C710.1, TP3.1 (1_1), U2.25 (SYS); also elsewhere on the board
GND: C9.2, C10.2, C11.2, C12.2, C192.2, C700.2, C701.2, C702.2, C703.2, C704.2, C705.2, C706.2, C707.2, C708.2, C709.2, C710.2, C711.2, C712.2, C713.2, C714.2, C720.2, C721.2, C722.2, C723.2, C725.2, C740.2, C741.2, C742.2, C743.2, C744.2, C745.2, C746.2, C795.2, C796.2, C797.2, C798.2, C799.2, D190.2 (A2), J190.2, Q700.2 (S), Q701.2 (S), Q702.2 (S), R13.2, R18.2, R184.1, R190.2, R192.2, R702.2, R705.2, R709.2, R710.2, R713.2, R719.2, R732.2, R735.2, R740.2, R797.2, R798.2, RS1.2, TP1.1 (1_1), U2.10 (ACDRV2), U2.11 (ACDRV1), U2.27 (GND), U11.4 (RETRY), U11.5 (GND), U12.8 (GND), U12.11 (MODE), U12.25 (GND), U15.7 (GND), U15.20 (HYS), U15.21 (EP/GND), U718.8 (GND); also elsewhere on the board

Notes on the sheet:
== 3S cell entry, autonomous primary protection, fuse and redundant pack protection ==
== U10 BQ34Z100-G1 3S fuel gauge for protected external pack ==
== U2 bq25798 Buck-Boost Charger / NVDC Power Path (VSYS) ==
== U15 LTC4418IUF: USB-C PD priority over protected AUX/solar ==
J190 is the single AUX/SOLAR physical input; USB-C PD negotiation remains only on sheet 5.
TPS26630 accepts 7-22V nominal; 0.1% ladder targets 5.53V/22.99V rising UV/OV and a 3A limit.
U15 validates USB near 15V and AUX across 7-22V, gives USB priority, and prevents inactive-source backfeed.
SMCJ24CA protects the 67V eFuse input; active OVP protects the BQ25798 24V recommended input limit.
NOTE: no wires used - connectivity is via matching label names (valid KiCad practice).
J2: pins 1/2 PACK+, pins 3/4 PACK-, pin 5 cell1 tap, pin 6 cell2 tap. Verify harness order before first connection.
U719 BQ7791500 autonomously protects each cell at 4.20V OV / 2.90V UV and drives back-to-back low-side FETs.
RS11=8mOhm gives 7.5A nominal OCD and 15A nominal SCD; U11/RS10 and F1 remain independent tighter/secondary protection.
No motherboard battery thermistors are fitted. U719 TS uses TI's 10k-to-VSS unused-function connection; VTB is NC.
BQ25798 /CE is fail-off: REGN pulls it high; active-high CHG_ENABLE turns Q700 on only after EC source validation.
U2 ILIM_HIZ divider is a 3.0A hardware ceiling; EC programs a lower IINDPM from the selected TPS25751A Active PDO Contract (0x31).
J190 is the one 7-22V nominal AUX/solar input; TPS26630 protects it before BQ25798.
Solar MPPT is implemented by BQ25798 firmware on this same input; there is no second charger path.
AUX_DC_ADC measures the post-reverse-FET input so firmware can detect droop and reduce BQ25798 input current.
U2 VAC1/VAC2 tie to VBUS_COMBINED in no-external-mux mode; ACDRV1/2 go to GND.
Q25 follows BQ25798EVM-842: SDRV disconnects pack discharge for electronic ship/hard-off while adapter charging can wake the pack.
U11 accepts about 8.45-13.57V nominal; 11mOhm RS10 gives 4.55A nominal and <=5.51A worst-case trips.
BQ25798 TS is fixed at 58.9% REGN by 5.24k/7.50k; firmware sets TS_IGNORE=1. BQ34Z100 TS has 10k to VSS; set TEMPS=0.
MANDATORY STARTUP: hold MU_12V_ENABLE low; read TPS25751A PD Status 0x35 plus Active PDO/RDO 0x31/0x32; program VSYSMIN and IINDPM <= min(PDO-0.25A, 2.75A); require VSYS >=10.0V.
Then assert MU_12V_ENABLE and require MU_12V_PG within 20ms. Any PG timeout, source-invalid, charger fault, watchdog fault, or VSYS<10V disables the Mu rail.
BQ25798 firmware must set STOP_WD_CHG=1 and TS_IGNORE=1, service faults, validate PDO current, and assert CHG_ENABLE only after safe limits are programmed.
U718 is the aggregate AON safety boundary: 1.51A typical limit, true reverse blocking, 6.20V nominal UVLO, and 22.40V nominal OVLO.
AON UVLO corners are 6.06-6.36V: default 5V USB-C is negotiation-only; TPS25751A dead-battery boot must obtain a valid higher-voltage PDO before EC_AON_IN starts.
A 5V-only USB-C source leaves the laptop off. AON_FAULT_N inhibits charging and Mu start; the service connector remains the assembly hard disconnect.
C746 provides low-ESR hold-up through LTC4418 break-before-make source switching.
